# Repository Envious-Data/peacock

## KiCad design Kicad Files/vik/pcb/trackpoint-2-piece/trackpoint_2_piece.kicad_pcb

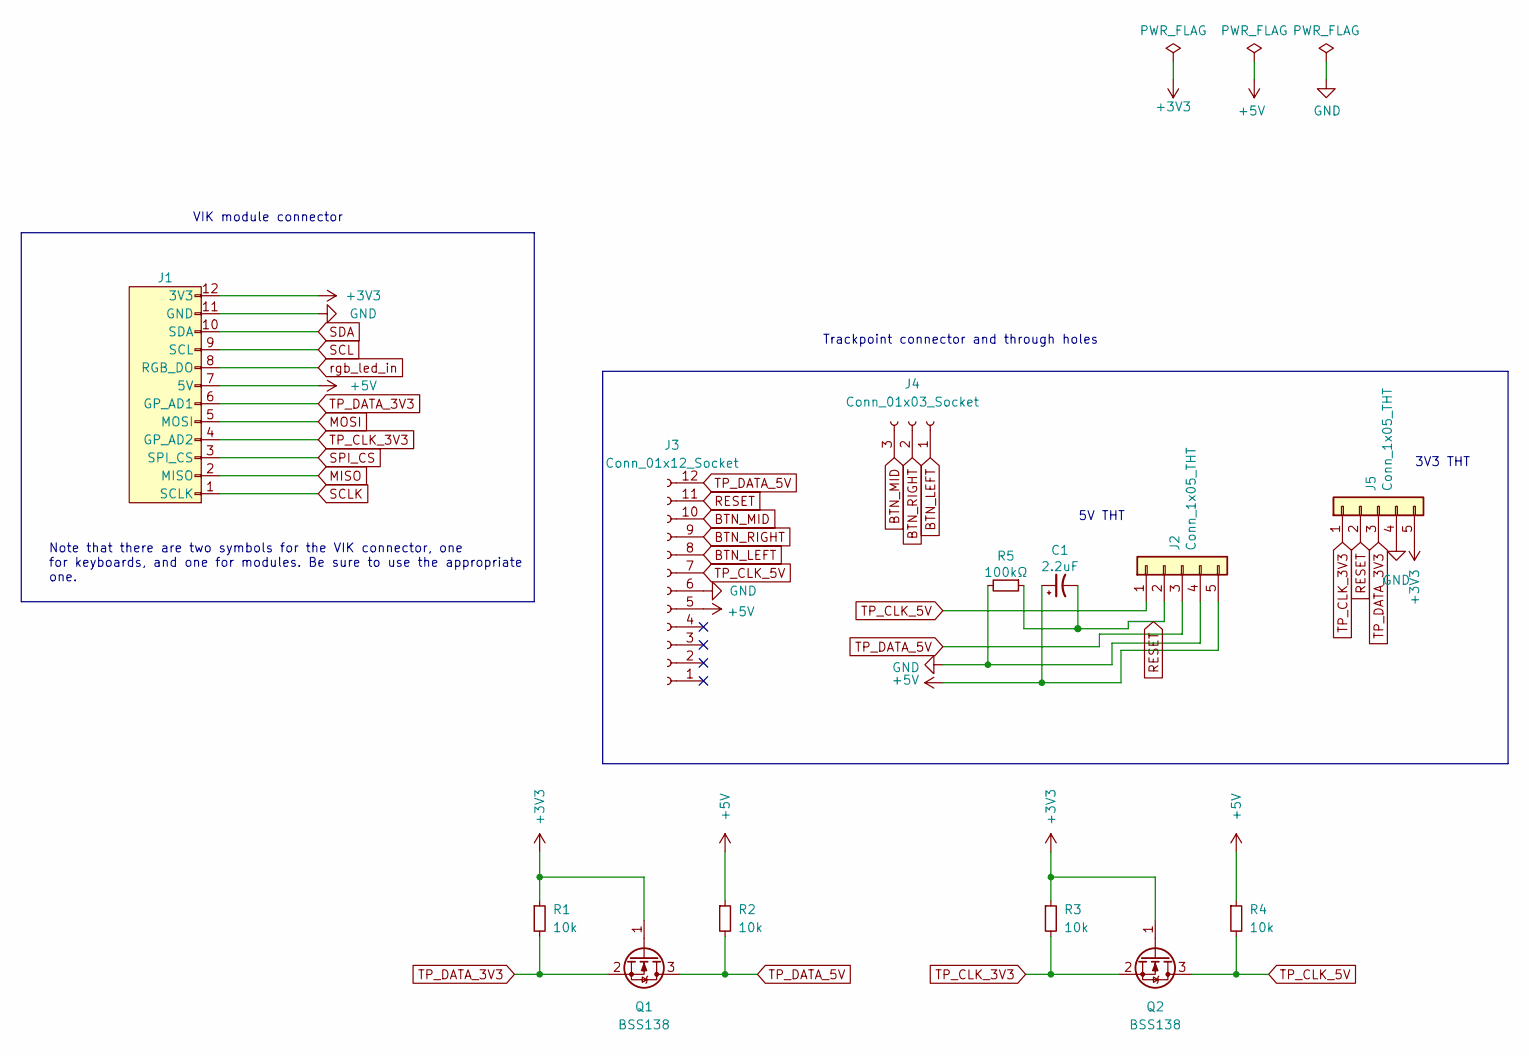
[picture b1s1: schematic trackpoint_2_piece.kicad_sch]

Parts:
C1: 2.2uF; C_0805_2012Metric_Pad1.18x1.45mm_HandSolder; LCSC C377773
J1: vik-module-connector-horizontal; LCSC C479750
J2, J5: Conn_1x05_THT; Connector_THT_1x5_2.54
J3: Conn_01x12_Socket; TE_1-84953-2_1x12-1MP_P1.0mm_Horizontal; LCSC C262367
J4: Conn_01x03_Socket; Connector_THT_1x3_2.54
Q1, Q2: BSS138; SOT-23; LCSC C78284
R1, R2, R3, R4: 10k; R_0805_2012Metric_Pad1.20x1.40mm_HandSolder; LCSC C17414
R5: 100kΩ; R_0805_2012Metric_Pad1.20x1.40mm_HandSolder; LCSC C149504

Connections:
+3V3: J1.12 (3V3), J5.5, Q1.1 (G), Q2.1 (G), R1.1, R3.1
+5V: C1.1, J1.7 (5V), J2.5, J3.5, R2.1, R4.1
BTN_LEFT: J3.8, J4.1
BTN_MID: J3.10, J4.3
BTN_RIGHT: J3.9, J4.2
GND: J1.11 (GND), J2.4, J3.6, J5.4, R5.2
MISO: J1.2 (MISO)
MOSI: J1.5 (MOSI)
RESET: C1.2, J2.2, J3.11, J5.2, R5.1
SCL: J1.9 (SCL)
SCLK: J1.1 (SCLK)
SDA: J1.10 (SDA)
SPI_CS: J1.3 (SPI_CS)
TP_CLK_3V3: J1.4 (GPIO_AD2), J5.1, Q2.2 (S), R3.2
TP_CLK_5V: J2.1, J3.7, Q2.3 (D), R4.2
TP_DATA_3V3: J1.6 (GPIO_AD1), J5.3, Q1.2 (S), R1.2
TP_DATA_5V: J2.3, J3.12, Q1.3 (D), R2.2
rgb_led_in: J1.8 (RGB_LED_IN)

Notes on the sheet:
5V THT
Note that there are two symbols for the VIK connector, one for keyboards, and one for modules. Be sure to use the appropriate one.
VIK module connector
3V3 THT
Trackpoint connector and through holes

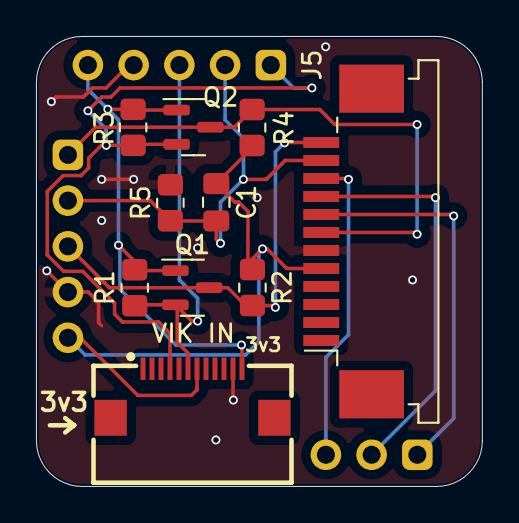
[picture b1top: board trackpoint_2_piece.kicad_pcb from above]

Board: 2 copper layers, 24.8 x 25.0 mm, 13 parts (0 on the bottom side), 11 nets.

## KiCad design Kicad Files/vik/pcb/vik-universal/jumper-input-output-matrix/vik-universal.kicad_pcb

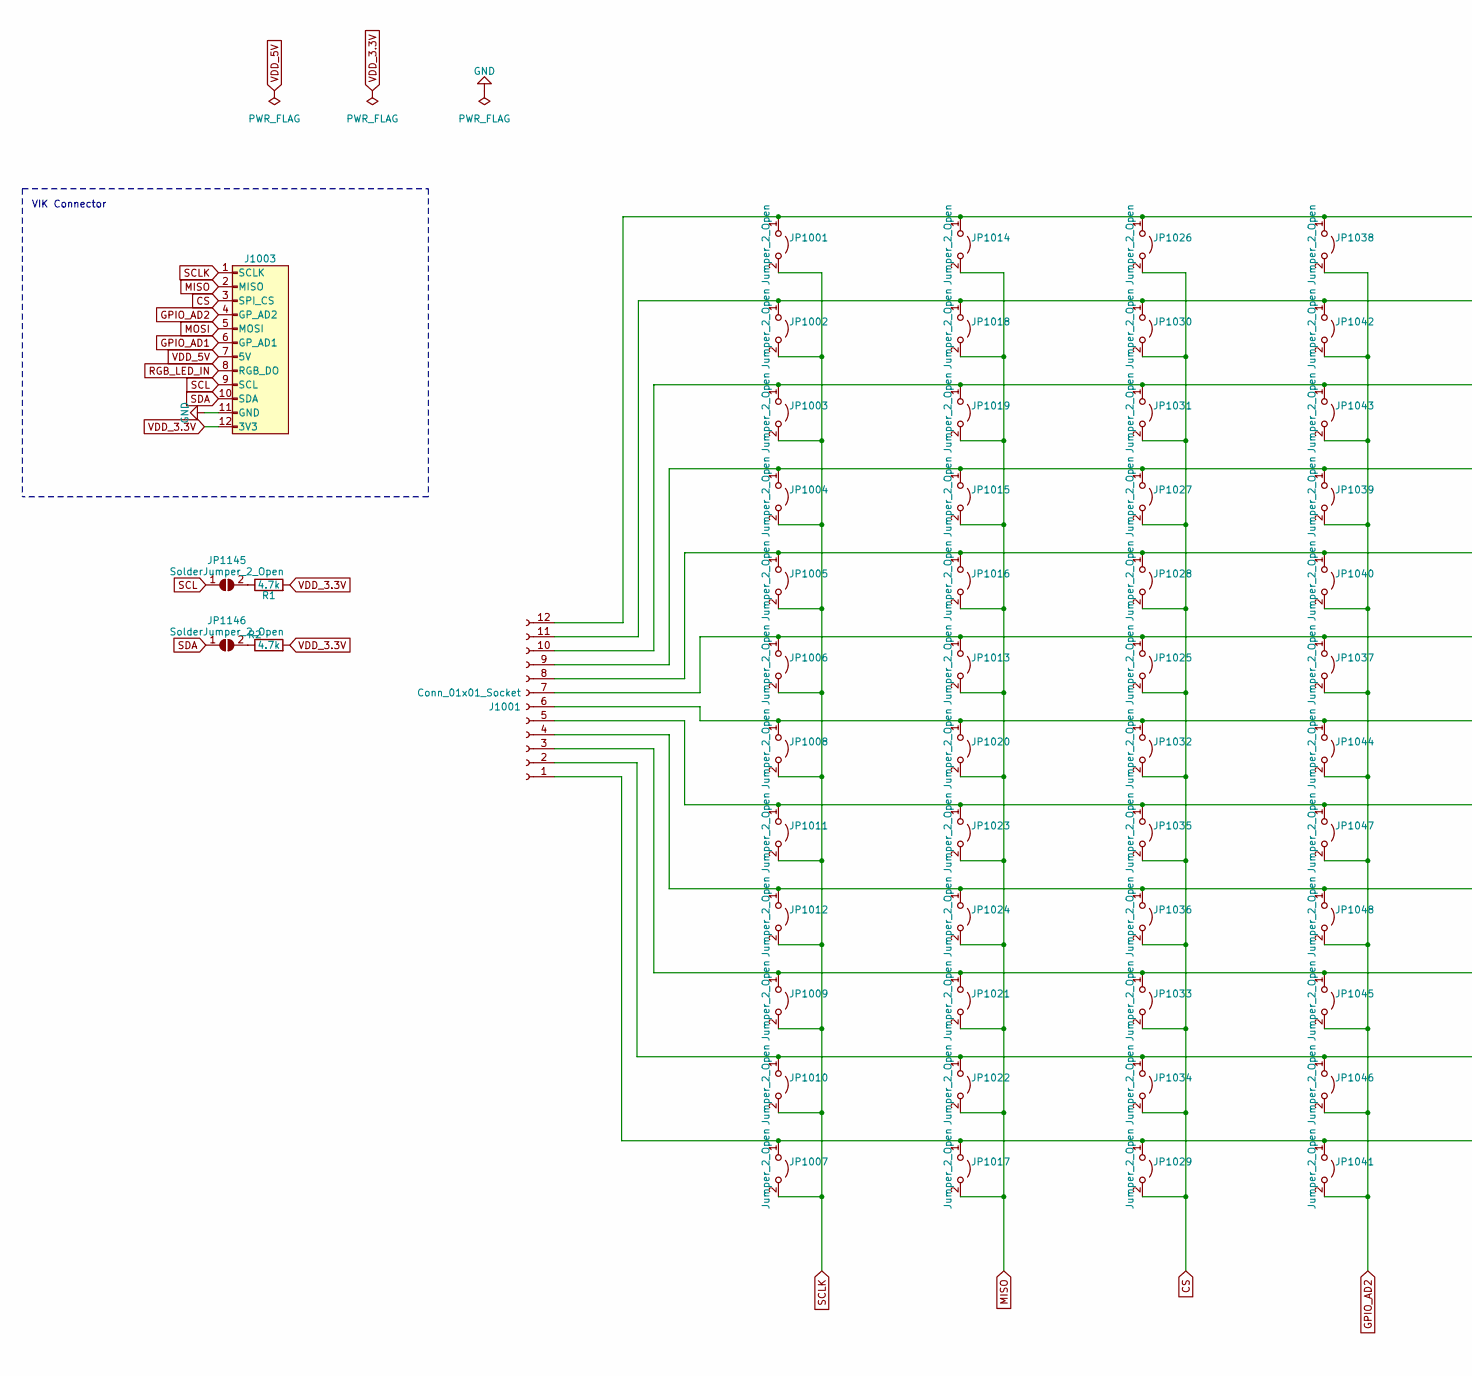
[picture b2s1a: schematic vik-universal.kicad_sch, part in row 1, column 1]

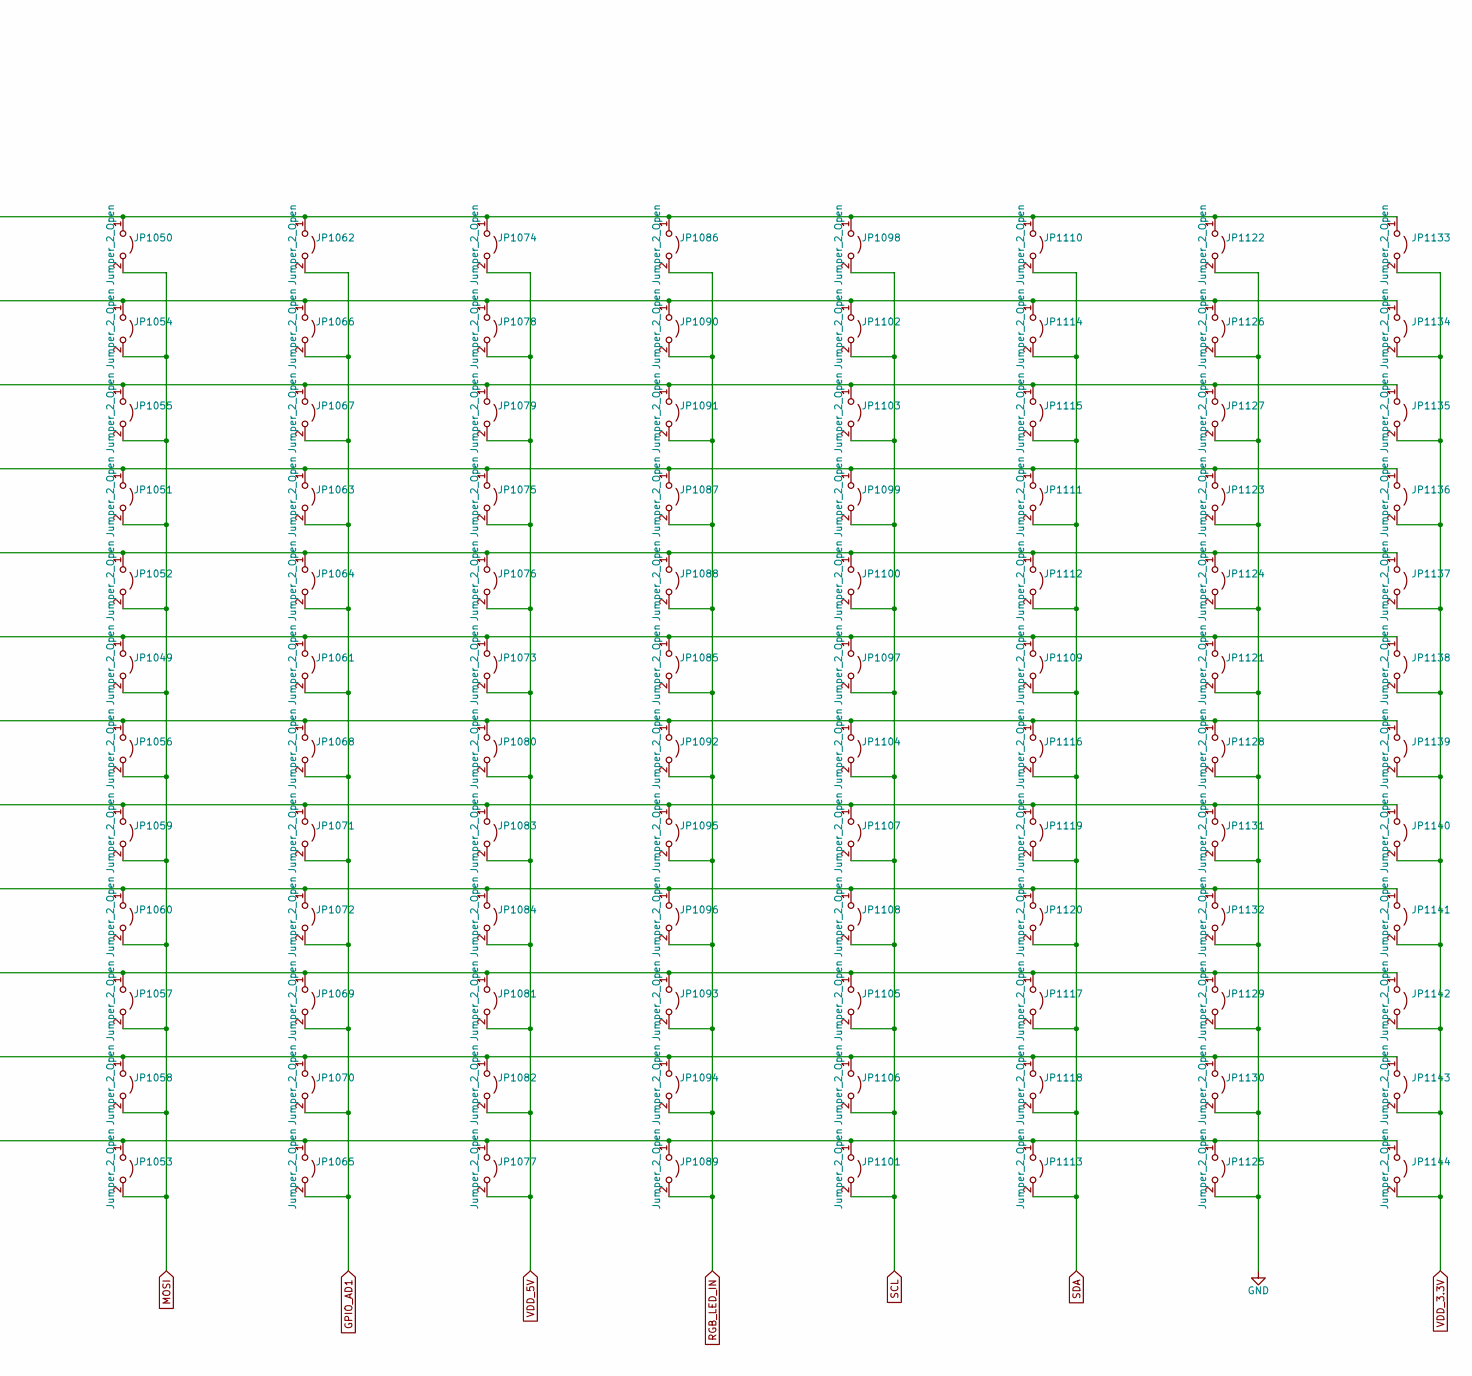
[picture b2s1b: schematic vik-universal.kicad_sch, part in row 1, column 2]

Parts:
J1001: Conn_01x01_Socket; PinSocket_1x12_P2.54mm_Vertical
J1003: vik-module-connector-horizontal; LCSC C2919557
JP1001, JP1002, JP1003, JP1004, JP1005, JP1006, JP1007, JP1008, JP1009, JP1010, JP1011, JP1012, JP1013, JP1014, JP1015, JP1016, JP1017, JP1018, JP1019, JP1020, JP1021, JP1022, JP1023, JP1024, JP1025, JP1026, JP1027, JP1028, JP1029, JP1030, JP1031, JP1032, JP1033, JP1034, JP1035, JP1036, JP1037, JP1038, JP1039, JP1040, JP1041, JP1042, JP1043, JP1044, JP1045, JP1046, JP1047, JP1048, JP1049, JP1050, JP1051, JP1052, JP1053, JP1054, JP1055, JP1056, JP1057, JP1058, JP1059, JP1060, JP1061, JP1062, JP1063, JP1064, JP1065, JP1066, JP1067, JP1068, JP1069, JP1070, JP1071, JP1072, JP1073, JP1074, JP1075, JP1076, JP1077, JP1078, JP1079, JP1080, JP1081, JP1082, JP1083, JP1084, JP1085, JP1086, JP1087, JP1088, JP1089, JP1090, JP1091, JP1092, JP1093, JP1094, JP1095, JP1096, JP1097, JP1098, JP1099, JP1100, JP1101, JP1102, JP1103, JP1104, JP1105, JP1106, JP1107, JP1108, JP1109, JP1110, JP1111, JP1112, JP1113, JP1114, JP1115, JP1116, JP1117, JP1118, JP1119, JP1120, JP1121, JP1122, JP1123, JP1124, JP1125, JP1126, JP1127, JP1128, JP1129, JP1130, JP1131, JP1132, JP1133, JP1134, JP1135, JP1136, JP1137, JP1138, JP1139, JP1140, JP1141, JP1142, JP1143, JP1144: Jumper_2_Open; SolderJumper-2_P1.3mm_Open_RoundedPad1.0x1.5mm
JP1145, JP1146: SolderJumper_2_Open; SolderJumper-2_P1.3mm_Open_RoundedPad1.0x1.5mm
R1, R2: 4.7k; D3_TH_SMD; LCSC C104821

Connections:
CS: J1003.3 (SPI_CS), JP1025.2 (B), JP1026.2 (B), JP1027.2 (B), JP1028.2 (B), JP1029.2 (B), JP1030.2 (B), JP1031.2 (B), JP1032.2 (B), JP1033.2 (B), JP1034.2 (B), JP1035.2 (B), JP1036.2 (B)
GND: J1003.11 (GND), JP1121.2 (B), JP1122.2 (B), JP1123.2 (B), JP1124.2 (B), JP1125.2 (B), JP1126.2 (B), JP1127.2 (B), JP1128.2 (B), JP1129.2 (B), JP1130.2 (B), JP1131.2 (B), JP1132.2 (B)
GPIO_AD1: J1003.6 (GPIO_AD1), JP1061.2 (B), JP1062.2 (B), JP1063.2 (B), JP1064.2 (B), JP1065.2 (B), JP1066.2 (B), JP1067.2 (B), JP1068.2 (B), JP1069.2 (B), JP1070.2 (B), JP1071.2 (B), JP1072.2 (B)
GPIO_AD2: J1003.4 (GPIO_AD2), JP1037.2 (B), JP1038.2 (B), JP1039.2 (B), JP1040.2 (B), JP1041.2 (B), JP1042.2 (B), JP1043.2 (B), JP1044.2 (B), JP1045.2 (B), JP1046.2 (B), JP1047.2 (B), JP1048.2 (B)
MISO: J1003.2 (MISO), JP1013.2 (B), JP1014.2 (B), JP1015.2 (B), JP1016.2 (B), JP1017.2 (B), JP1018.2 (B), JP1019.2 (B), JP1020.2 (B), JP1021.2 (B), JP1022.2 (B), JP1023.2 (B), JP1024.2 (B)
MOSI: J1003.5 (MOSI), JP1049.2 (B), JP1050.2 (B), JP1051.2 (B), JP1052.2 (B), JP1053.2 (B), JP1054.2 (B), JP1055.2 (B), JP1056.2 (B), JP1057.2 (B), JP1058.2 (B), JP1059.2 (B), JP1060.2 (B)
unnamed: J1001.1, JP1007.1 (A), JP1017.1 (A), JP1029.1 (A), JP1041.1 (A), JP1053.1 (A), JP1065.1 (A), JP1077.1 (A), JP1089.1 (A), JP1101.1 (A), JP1113.1 (A), JP1125.1 (A), JP1144.1 (A)
unnamed: J1001.2, JP1010.1 (A), JP1022.1 (A), JP1034.1 (A), JP1046.1 (A), JP1058.1 (A), JP1070.1 (A), JP1082.1 (A), JP1094.1 (A), JP1106.1 (A), JP1118.1 (A), JP1130.1 (A), JP1143.1 (A)
unnamed: J1001.3, JP1009.1 (A), JP1021.1 (A), JP1033.1 (A), JP1045.1 (A), JP1057.1 (A), JP1069.1 (A), JP1081.1 (A), JP1093.1 (A), JP1105.1 (A), JP1117.1 (A), JP1129.1 (A), JP1142.1 (A)
unnamed: J1001.4, JP1012.1 (A), JP1024.1 (A), JP1036.1 (A), JP1048.1 (A), JP1060.1 (A), JP1072.1 (A), JP1084.1 (A), JP1096.1 (A), JP1108.1 (A), JP1120.1 (A), JP1132.1 (A), JP1141.1 (A)
unnamed: J1001.5, JP1011.1 (A), JP1023.1 (A), JP1035.1 (A), JP1047.1 (A), JP1059.1 (A), JP1071.1 (A), JP1083.1 (A), JP1095.1 (A), JP1107.1 (A), JP1119.1 (A), JP1131.1 (A), JP1140.1 (A)
unnamed: J1001.6, JP1008.1 (A), JP1020.1 (A), JP1032.1 (A), JP1044.1 (A), JP1056.1 (A), JP1068.1 (A), JP1080.1 (A), JP1092.1 (A), JP1104.1 (A), JP1116.1 (A), JP1128.1 (A), JP1139.1 (A)
unnamed: J1001.7, JP1006.1 (A), JP1013.1 (A), JP1025.1 (A), JP1037.1 (A), JP1049.1 (A), JP1061.1 (A), JP1073.1 (A), JP1085.1 (A), JP1097.1 (A), JP1109.1 (A), JP1121.1 (A), JP1138.1 (A)
unnamed: J1001.8, JP1005.1 (A), JP1016.1 (A), JP1028.1 (A), JP1040.1 (A), JP1052.1 (A), JP1064.1 (A), JP1076.1 (A), JP1088.1 (A), JP1100.1 (A), JP1112.1 (A), JP1124.1 (A), JP1137.1 (A)
unnamed: J1001.9, JP1004.1 (A), JP1015.1 (A), JP1027.1 (A), JP1039.1 (A), JP1051.1 (A), JP1063.1 (A), JP1075.1 (A), JP1087.1 (A), JP1099.1 (A), JP1111.1 (A), JP1123.1 (A), JP1136.1 (A)
unnamed: J1001.10, JP1003.1 (A), JP1019.1 (A), JP1031.1 (A), JP1043.1 (A), JP1055.1 (A), JP1067.1 (A), JP1079.1 (A), JP1091.1 (A), JP1103.1 (A), JP1115.1 (A), JP1127.1 (A), JP1135.1 (A)
unnamed: J1001.11, JP1002.1 (A), JP1018.1 (A), JP1030.1 (A), JP1042.1 (A), JP1054.1 (A), JP1066.1 (A), JP1078.1 (A), JP1090.1 (A), JP1102.1 (A), JP1114.1 (A), JP1126.1 (A), JP1134.1 (A)
unnamed: J1001.12, JP1001.1 (A), JP1014.1 (A), JP1026.1 (A), JP1038.1 (A), JP1050.1 (A), JP1062.1 (A), JP1074.1 (A), JP1086.1 (A), JP1098.1 (A), JP1110.1 (A), JP1122.1 (A), JP1133.1 (A)
unnamed 18: JP1145.2 (B); also elsewhere on the board
unnamed 19: JP1146.2 (B); also elsewhere on the board
RGB_LED_IN: J1003.8 (RGB_LED_IN), JP1085.2 (B), JP1086.2 (B), JP1087.2 (B), JP1088.2 (B), JP1089.2 (B), JP1090.2 (B), JP1091.2 (B), JP1092.2 (B), JP1093.2 (B), JP1094.2 (B), JP1095.2 (B), JP1096.2 (B)
SCL: J1003.9 (SCL), JP1097.2 (B), JP1098.2 (B), JP1099.2 (B), JP1100.2 (B), JP1101.2 (B), JP1102.2 (B), JP1103.2 (B), JP1104.2 (B), JP1105.2 (B), JP1106.2 (B), JP1107.2 (B), JP1108.2 (B), JP1145.1 (A)
SCLK: J1003.1 (SCLK), JP1001.2 (B), JP1002.2 (B), JP1003.2 (B), JP1004.2 (B), JP1005.2 (B), JP1006.2 (B), JP1007.2 (B), JP1008.2 (B), JP1009.2 (B), JP1010.2 (B), JP1011.2 (B), JP1012.2 (B)
SDA: J1003.10 (SDA), JP1109.2 (B), JP1110.2 (B), JP1111.2 (B), JP1112.2 (B), JP1113.2 (B), JP1114.2 (B), JP1115.2 (B), JP1116.2 (B), JP1117.2 (B), JP1118.2 (B), JP1119.2 (B), JP1120.2 (B), JP1146.1 (A)
VDD_3.3V: J1003.12 (3V3), JP1133.2 (B), JP1134.2 (B), JP1135.2 (B), JP1136.2 (B), JP1137.2 (B), JP1138.2 (B), JP1139.2 (B), JP1140.2 (B), JP1141.2 (B), JP1142.2 (B), JP1143.2 (B), JP1144.2 (B); also elsewhere on the board
VDD_5V: J1003.7 (5V), JP1073.2 (B), JP1074.2 (B), JP1075.2 (B), JP1076.2 (B), JP1077.2 (B), JP1078.2 (B), JP1079.2 (B), JP1080.2 (B), JP1081.2 (B), JP1082.2 (B), JP1083.2 (B), JP1084.2 (B)

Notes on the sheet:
VIK Connector

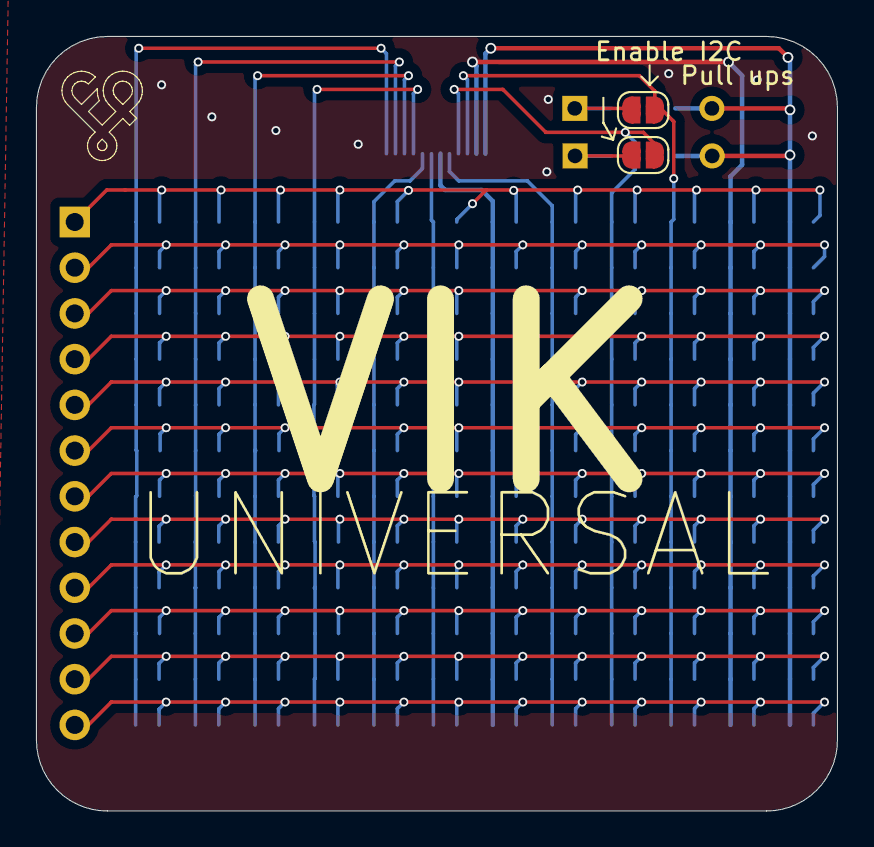
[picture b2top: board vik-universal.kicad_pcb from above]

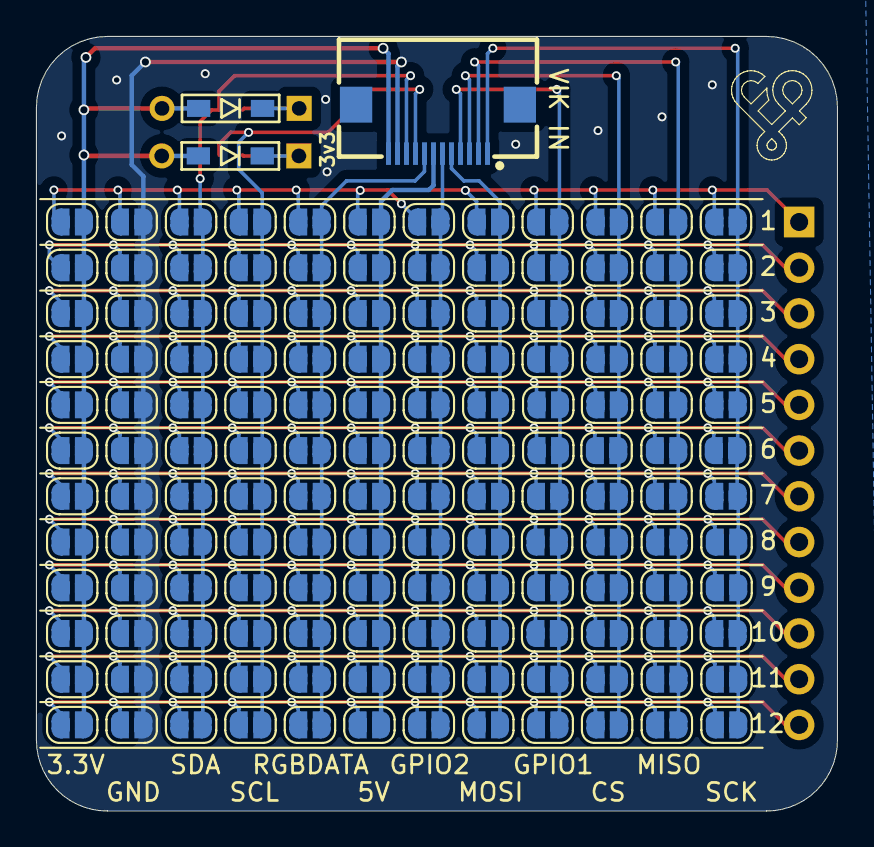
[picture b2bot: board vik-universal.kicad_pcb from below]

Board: 2 copper layers, 44.5 x 43.0 mm, 150 parts (148 on the bottom side), 26 nets.

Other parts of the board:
R1001, R1002: 4.7k; D3_TH_SMD

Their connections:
unnamed 18: R1001.1; also elsewhere on the board
unnamed 19: R1002.1; also elsewhere on the board
VDD_3.3V: R1001.2, R1002.2; also elsewhere on the board

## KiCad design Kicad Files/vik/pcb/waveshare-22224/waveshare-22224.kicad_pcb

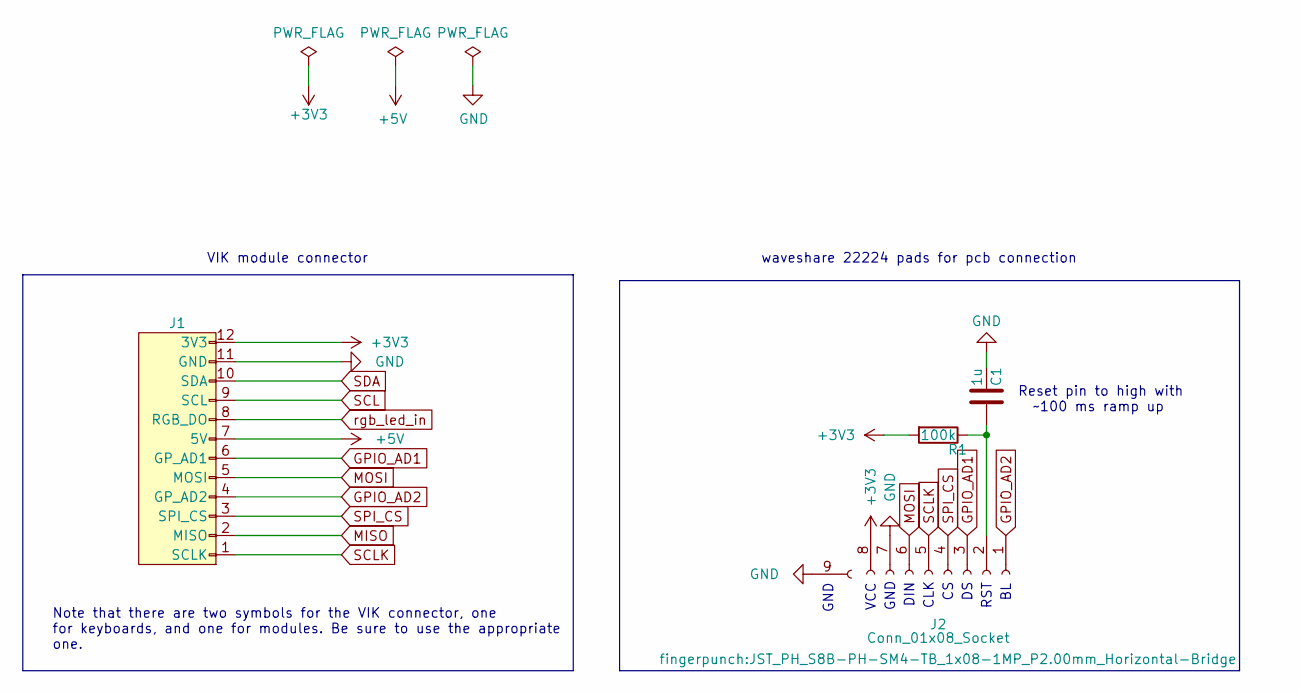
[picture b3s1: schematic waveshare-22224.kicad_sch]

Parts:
C1: 1u; C_0402_1005Metric; MPN CL05A105KA5NQNC; LCSC C52923
J1: vik-module-connector-horizontal; LCSC C479750
J2: Conn_01x08_Socket; JST_PH_S8B-PH-SM4-TB_1x08-1MP_P2.00mm_Horizontal-Bridge
R1: 100k; R_1206_3216Metric_Pad1.30x1.75mm_HandSolder; LCSC C17900

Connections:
+3V3: J1.12 (3V3), J2.8, R1.2
+5V: J1.7 (5V)
GND: C1.1, J1.11 (GND), J2.7, J2.9 (GND)
GPIO_AD1: J1.6 (GPIO_AD1), J2.3
GPIO_AD2: J1.4 (GPIO_AD2), J2.1
MISO: J1.2 (MISO)
MOSI: J1.5 (MOSI), J2.6
unnamed: C1.2, J2.2, R1.1
SCL: J1.9 (SCL)
SCLK: J1.1 (SCLK), J2.5
SDA: J1.10 (SDA)
SPI_CS: J1.3 (SPI_CS), J2.4
rgb_led_in: J1.8 (RGB_LED_IN)

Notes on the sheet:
DIN
RST
GND
Note that there are two symbols for the VIK connector, one for keyboards, and one for modules. Be sure to use the appropriate one.
waveshare 22224 pads for pcb connection
Reset pin to high with ~100 ms ramp up
CLK
VIK module connector
VCC

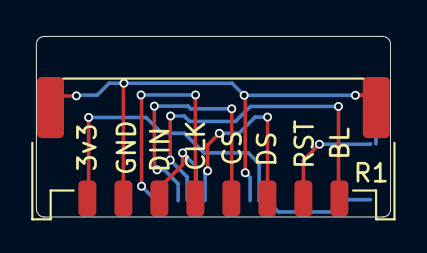
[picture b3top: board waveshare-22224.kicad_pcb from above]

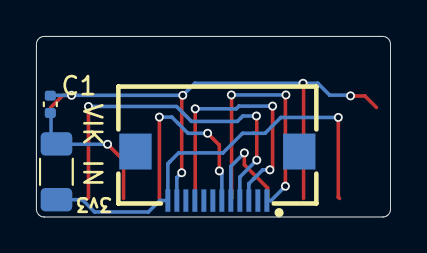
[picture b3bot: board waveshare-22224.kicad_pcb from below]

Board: 2 copper layers, 19.7 x 10.0 mm, 4 parts (3 on the bottom side), 8 nets.

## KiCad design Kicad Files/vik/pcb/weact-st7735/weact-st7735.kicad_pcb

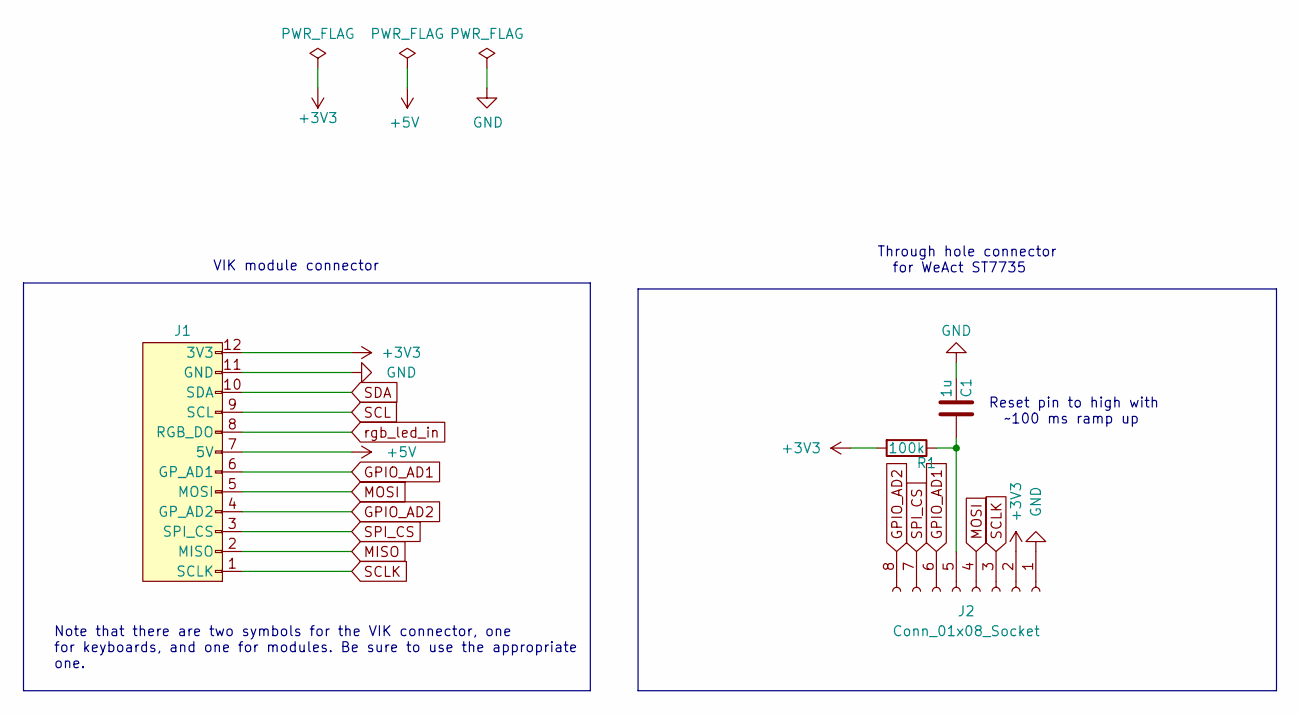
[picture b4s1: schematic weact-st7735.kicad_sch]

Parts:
C1: 1u; C_0402_1005Metric; MPN CL05A105KA5NQNC; LCSC C52923
J1: vik-module-connector-horizontal; LCSC C479750
J2: Conn_01x08_Socket; PinHeader_1x08_P2.54mm_Vertical
R1: 100k; R_1206_3216Metric_Pad1.30x1.75mm_HandSolder; LCSC C17900

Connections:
+3V3: J1.12 (3V3), J2.2, R1.2
+5V: J1.7 (5V)
GND: C1.1, J1.11 (GND), J2.1
GPIO_AD1: J1.6 (GPIO_AD1), J2.6
GPIO_AD2: J1.4 (GPIO_AD2), J2.8
MISO: J1.2 (MISO)
MOSI: J1.5 (MOSI), J2.4
unnamed: C1.2, J2.5, R1.1
SCL: J1.9 (SCL)
SCLK: J1.1 (SCLK), J2.3
SDA: J1.10 (SDA)
SPI_CS: J1.3 (SPI_CS), J2.7
rgb_led_in: J1.8 (RGB_LED_IN)

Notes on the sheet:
Note that there are two symbols for the VIK connector, one for keyboards, and one for modules. Be sure to use the appropriate one.
Through hole connector for WeAct ST7735
Reset pin to high with ~100 ms ramp up
VIK module connector

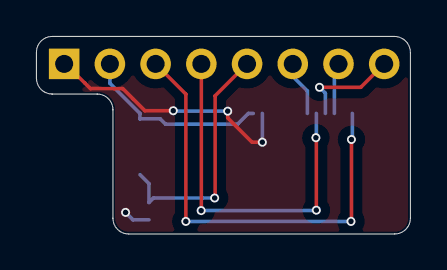
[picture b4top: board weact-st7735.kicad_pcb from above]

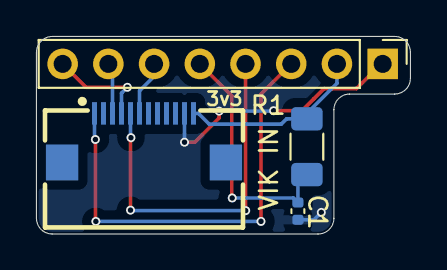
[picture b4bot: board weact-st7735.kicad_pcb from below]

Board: 2 copper layers, 20.8 x 11.0 mm, 4 parts (4 on the bottom side), 8 nets.

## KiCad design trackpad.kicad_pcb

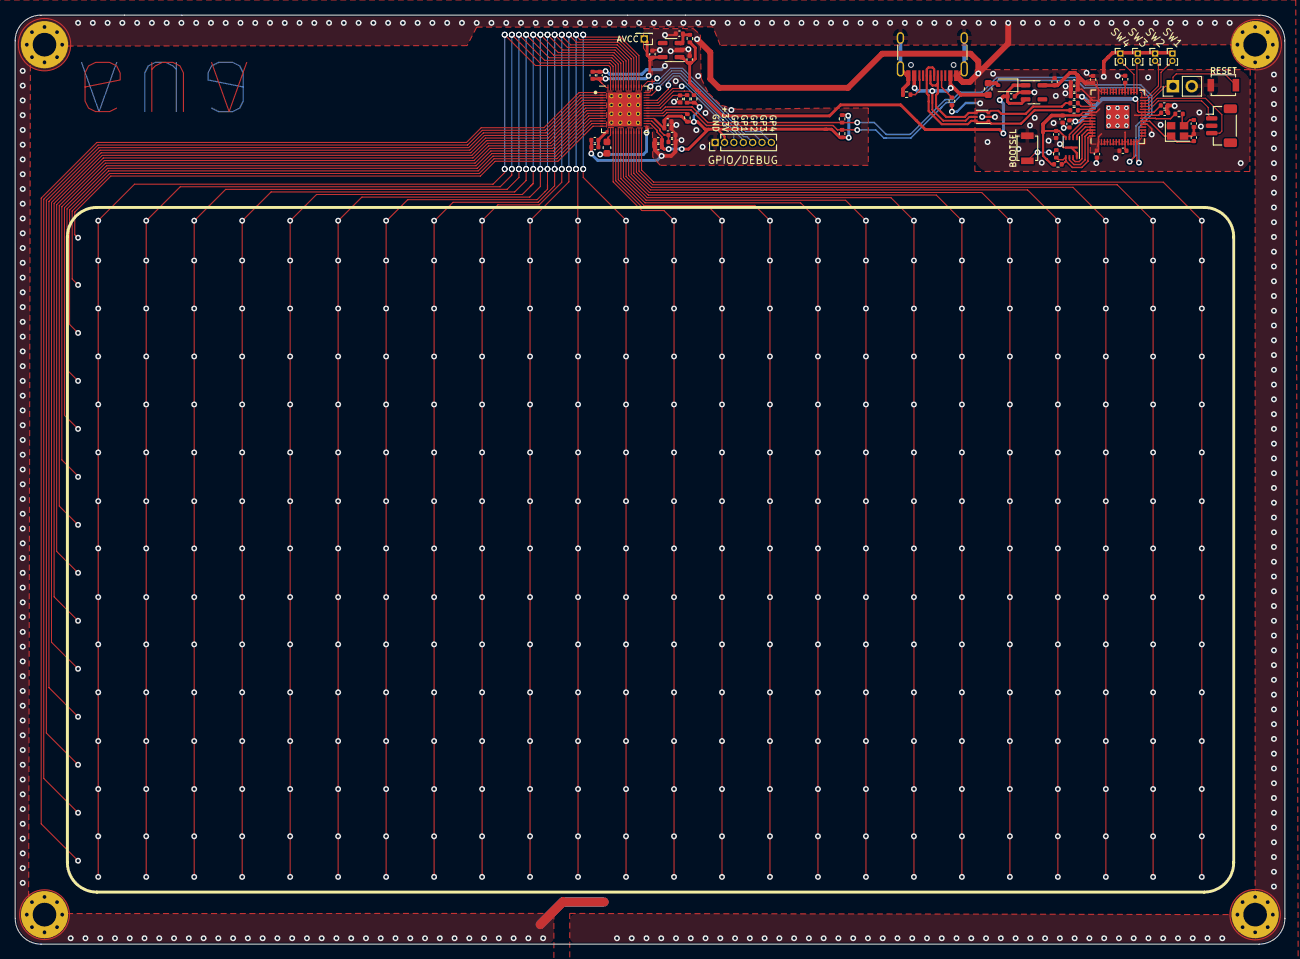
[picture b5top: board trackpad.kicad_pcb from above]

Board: 2 copper layers, 172.0 x 125.8 mm, 68 parts (0 on the bottom side), 46 nets.

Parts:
C1, C4, C14, C15, C18, C22, C28, C30: 1µ; C_0402_1005Metric
C2, C3, C5, C6, C7, C8, C9, C10, C11, C37: 100n; C_0402_1005Metric
C12, C13: 15p; C_0402_1005Metric
C16, C39: 10nF; C_0402_1005Metric
C17: 2.2nF; C_0603_1608Metric
C19, C21, C23, C25, C27: 22n; C_0402_1005Metric
C20, C24, C26: 2.2µ; C_0402_1005Metric
D1: B5817; D_SOD-323
F1: Polyfuse; Fuse_0603_1608Metric
H1, H2, H3, H4: MountingHole_Pad; MountingHole_3.2mm_M3_Pad_Via
J1: type-c-31-m-12; USB_C_Receptacle_HRO_TYPE-C-31-M-12
J3: JST 3P; JST_SH_BM03B-SRSS-TB_1x03-1MP_P1.00mm_Vertical
J5: Conn_01x07_Pin; PinHeader_1x07_P1.27mm_Vertical
J9: Conn_01x02_Pin; PinHeader_1x02_P2.54mm_Vertical
J10: Conn_01x01_Pin; PinHeader_1x01_P1.27mm_Vertical
R1, R11, R12, R17: 10k; R_0402_1005Metric
R2, R3: 1k; R_0402_1005Metric
R6, R7: 5.1k; R_0402_1005Metric
R8, R9: 27; R_0402_1005Metric
R10: 12k; R_0402_1005Metric
R13, R14: 3.3k; R_0402_1005Metric
SW1, SW2, SW3, SW4: SW_Push; PinHeader_1x02_P1.00mm_Vertical
SW_BOOT1: SW_Push; SW_SPST_B3U-1000P
SW_RST1: SW_Push; SW_SPST_B3U-1000P
U1: RP2040; QFN-56-1EP_7x7mm_P0.4mm_EP3.2x3.2mm
U2: W25Q16JVUXIQ; USON-8-1EP_3x2mm_P0.5mm_EP0.25x1.65mm
U3, U5: MIC5504-3.3YM5; SOT-23-5
U4: mXT336UD-MAU002; QFN-56_EP_6x6_Pitch0.35mm
U7: USBLC6-2P6; SOT-666
Y1: Crystal_GND24; Crystal_SMD_2520-4Pin_2.5x2.0mm

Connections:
3V3: C4.1, C5.1, C6.1, C7.1, C8.1, C9.1, C10.1, C11.1, C30.1, C37.2, R1.1, U1.1 (IOVDD), U1.10 (IOVDD), U1.22 (IOVDD), U1.33 (IOVDD), U1.42 (IOVDD), U1.43 (ADC_AVDD), U1.44 (VREG_IN), U1.48 (USB_VDD), U1.49 (IOVDD), U2.8 (VCC), U3.5 (VOUT)
5V: C14.1, C15.1, D1.1 (K), R17.1, U3.1 (VIN), U3.3 (EN), U5.1 (VIN)
+1V1: C1.1, C2.1, C3.1, U1.23 (DVDD), U1.45 (VREG_VOUT), U1.50 (DVDD)
+3.3VA: C20.2, C21.2, C28.1, J10.1, U4.56 (AVDD), U5.5 (VOUT)
+3V3: C24.2, C25.2, C26.2, C27.2, J5.2, R10.1, R11.1, R12.1, R13.1, R14.1, U4.30 (VDD), U4.32 (VDDIO)
/Macropad/D+: J1.A6 (D+), J1.B6 (D+), R8.2, U7.1 (I/O1), U7.6 (I/O1)
/Macropad/D-: J1.A7 (D-), J1.B7 (D-), R9.2, U7.3 (I/O2), U7.4 (I/O2)
/Macropad/RUN: J9.1, SW_RST1.1, U1.26 (RUN)
/Macropad/SW1: SW1.2, U1.27 (GPIO16)
/Macropad/SW2: SW2.2, U1.28 (GPIO17)
/Macropad/SW3: SW3.2, U1.29 (GPIO18)
/Macropad/SW4: SW4.2, U1.30 (GPIO19)
/Sensor/CHANGE: R11.2, U4.37 (CHG)
/Sensor/GPIO0: J5.3, U4.38 (GPIO0)
/Sensor/GPIO1: J5.4, U4.39 (GPIO1)
/Sensor/GPIO2: J5.5, U4.41 (GPIO2)
/Sensor/GPIO3: J5.6, U4.42 (GPIO3)
/Sensor/GPIO4: J5.7, U4.43 (GPIO4)
/Sensor/RESET: C16.1, R10.2, U4.36 (RESET)
GND: C1.2, C2.2, C3.2, C4.2, C5.2, C6.2, C7.2, C8.2, C9.2, C10.2, C11.2, C12.2, C13.2, C14.2, C15.2, C16.2, C18.2, C19.2, C20.1, C21.1, C22.1, C23.1, C24.1, C25.1, C26.1, C27.1, C28.2, C30.2, C37.1, C39.2, H1.1, H2.1, H3.1, H4.1, J1.A1 (GND), J1.A12 (GND), J1.B1 (GND), J1.B12 (GND), J1.S1 (SHIELD), J3.2, J5.1, J9.2, R6.2, R7.2, SW1.1, SW2.1, SW3.1, SW4.1, SW_BOOT1.1, SW_RST1.2, U1.19 (TESTEN), U1.57 (GND), U2.4 (GND), U2.9 (EP), U3.2 (GND), U4.57 (GND), U5.2 (GND), U7.2 (GND), Y1.2, Y1.4
unnamed: C13.1, R3.2, Y1.3
unnamed: D1.2 (A), F1.1
unnamed: J1.A5 (CC1), R6.1
unnamed: J1.B5 (CC2), R7.1
unnamed: J3.1, U1.24 (SWCLK)
unnamed: J3.3, U1.25 (SWD)
unnamed: R2.1, SW_BOOT1.2
unnamed: U1.52 (QSPI_SCLK), U2.6 (CLK)
unnamed: U1.53 (QSPI_SD0), U2.5 (DI(IO0))
unnamed: U1.55 (QSPI_SD1), U2.2 (DO(IO1))
unnamed: U1.54 (QSPI_SD2), U2.3 (IO2)
unnamed: U1.51 (QSPI_SD3), U2.7 (IO3)
unnamed: R1.2, R2.2, U1.56 (QSPI_SS), U2.1 (~CS)
unnamed: R9.1, U1.46 (USB_DM)
unnamed: R8.1, U1.47 (USB_DP)
unnamed: C12.1, U1.20 (XIN), Y1.1
unnamed: R3.1, U1.21 (XOUT)
unnamed: C17.2, U4.29 (EXCAP0)
unnamed: C17.1, U4.16 (EXCAP1)
unnamed: R12.2, U4.33 (TEST)
unnamed: C22.2, C23.2, U4.31 (VDDCORE)
unnamed: C18.1, C19.1, U4.15 (XVDD)
unnamed: C39.1, R17.2, U5.3 (EN)
SCL: R13.2, U1.14 (GPIO11), U4.35 (SCL)
SDA: R14.2, U1.13 (GPIO10), U4.34 (SDA)
VBUS: F1.2, J1.A4 (VBUS), J1.A9 (VBUS), J1.B4 (VBUS), J1.B9 (VBUS), U7.5 (VBUS)

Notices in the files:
Kicad Files/vik/pcb/vik-universal/breadboard/vik-universal.kicad_sch:
Copyright Quentin Lebastard
